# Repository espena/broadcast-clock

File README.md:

# Broadcast clock

**Digital precision studio/broadcast master clock with WiFi configuration, NTP client/server and GPS time sync.**

## Details

You'll find a complete project description on [my personal home page](https://espenandersen.no/esp32-broadcast-clock/ "Broadcast clock with ESP32 and NTP/GPS time receiver").

The enclosure is an 25x25 cm [IKEA "Sannahed"](https://www.ikea.com/us/en/p/sannahed-frame-black-60459118/) photo frame, which is deep enough to encapsulate the circuitry. I replaced the provided plexi glass with a dark acrylic glass plate.

There are no traditional buttons to control the clock. Instead, it has a browser based web configurator. When powered on, the clock will expose a dedicated wifi network for 30 seconds. Connect to the network in order to access the clock's control panel.

The clock supports time synchronization over the web (NTP) or via a range of GNSS satellite systems (GPS/QZSS, GLONASS, BeiDou, Galileo). It acts as a highly accurate NTP time server for other clocks on your LAN.

LED brightness is auto-adjusted to ambient light conditions. This feature can be overridden in the control panel.

It also has a stopwatch and a countdown timer that is operated from the browser interface.

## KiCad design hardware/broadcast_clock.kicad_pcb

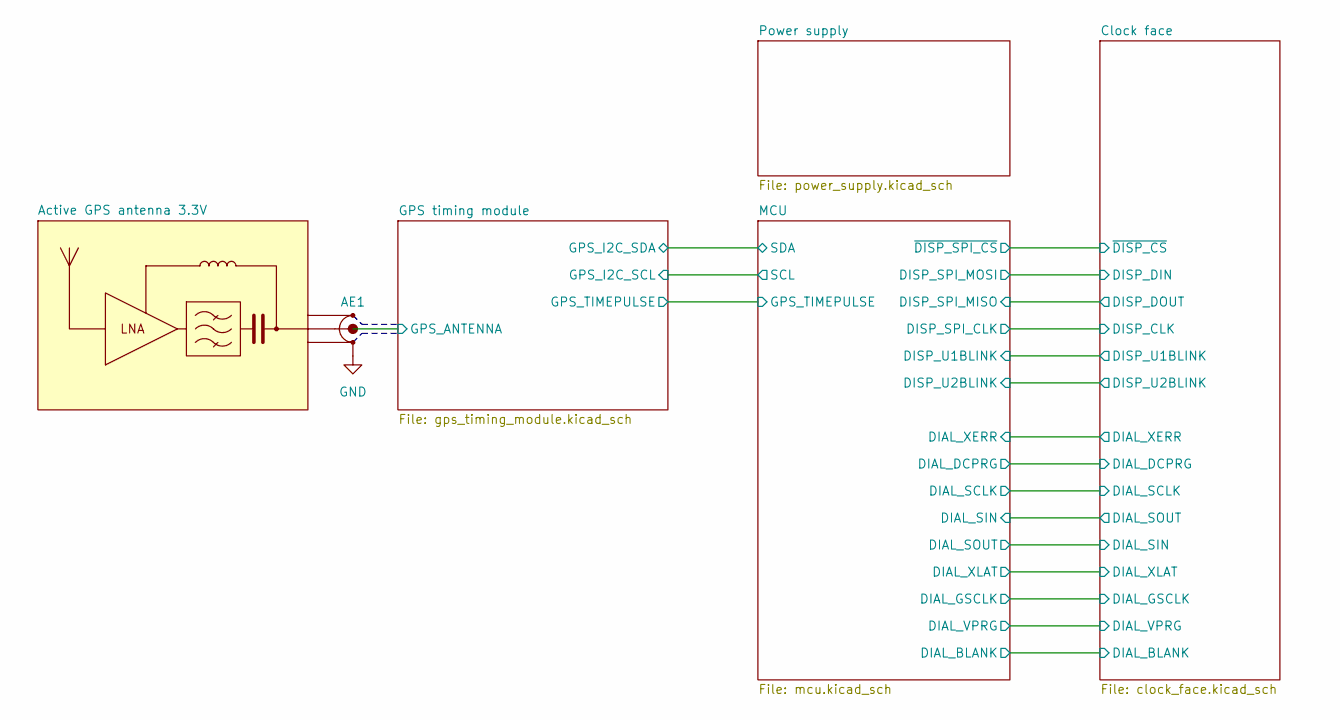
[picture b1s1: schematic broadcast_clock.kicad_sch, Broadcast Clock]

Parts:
AE1: Active GPS antenna 3.3V; SMA_Amphenol_132291-12_Vertical

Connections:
/GPS timing module/GPS_ANTENNA: AE1.1 (ANT); also elsewhere on the board

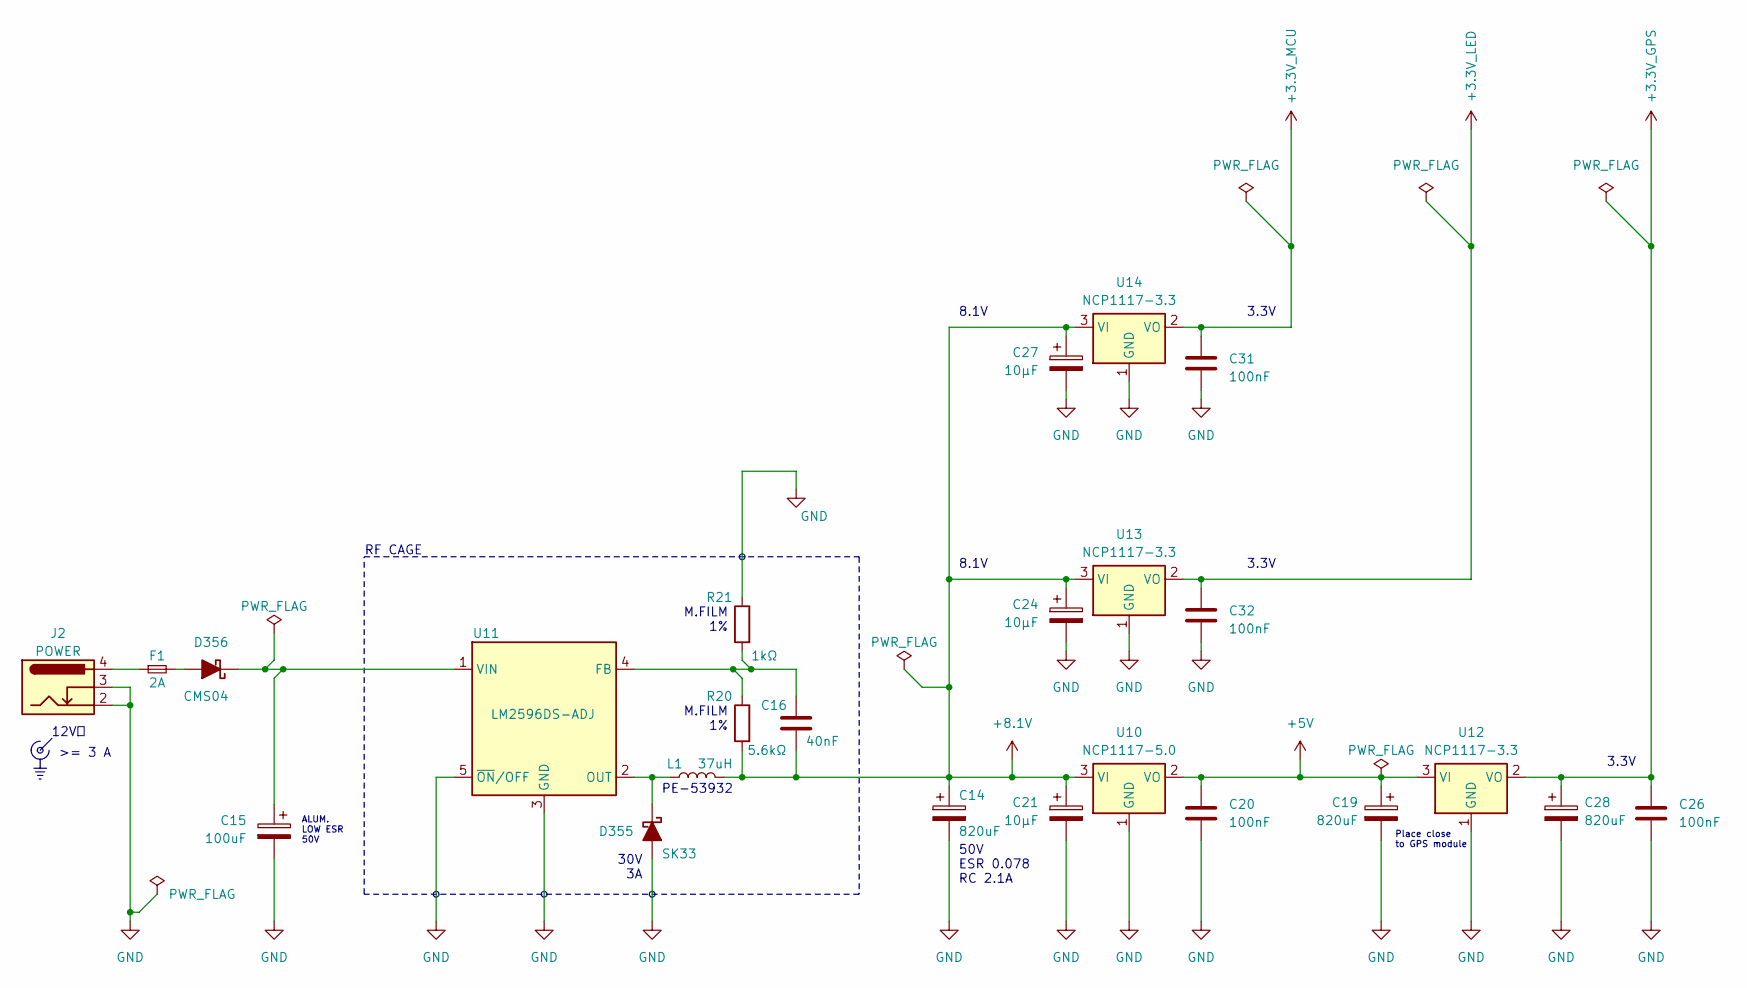
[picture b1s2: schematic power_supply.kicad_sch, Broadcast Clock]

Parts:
C14, C19, C28: 820uF; CP_Elec_18x16.5
C15: 100uF; CP_Elec_8x10
C16: 40nF; C_0805_2012Metric
C20, C26, C31, C32: 100nF; C_0805_2012Metric
C21, C24, C27: 10µF; C_0805_2012Metric
D355: SK33; D_SMA
D356: CMS04; SODFL4724X108N
F1: 2A; FuseHolder_Keystone_3554
J2: POWER; BarrelJack_DC044_Horizontal
L1: 37uH; L_Pulse_LCI-44
R20: 5.6kΩ; R_0805_2012Metric
R21: 1kΩ; R_0805_2012Metric
U10: NCP1117-5.0; SOT-223-3_TabPin2
U11: LM2596DS-ADJ; NCP5663DSADJR4G
U12, U13, U14: NCP1117-3.3; SOT-223-3_TabPin2

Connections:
+3.3V_GPS: C26.1, C28.1, U12.2 (VO); also elsewhere on the board
+5V: C19.1, C20.1, U10.2 (VO), U12.3 (VI)
+8.1V: C14.1, C16.2, C21.1, C24.1, C27.1, L1.2, R20.2, U10.3 (VI), U13.3 (VI), U14.3 (VI)
unnamed: D355.1 (K), L1.1, U11.2 (OUT)
unnamed: D356.2 (A), F1.2
unnamed: C15.1, D356.1 (K), U11.1 (VIN)
unnamed: F1.1, J2.4
unnamed: C16.1, R20.1, R21.2, U11.4 (FB)

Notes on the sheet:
M.FILM 1%
3.3V
ALUM. LOW ESR 50V
PE-53932
Place close to GPS module
RF CAGE
12V⎓
30V 3A
8.1V
>= 3 A
50V ESR 0.078 RC 2.1A

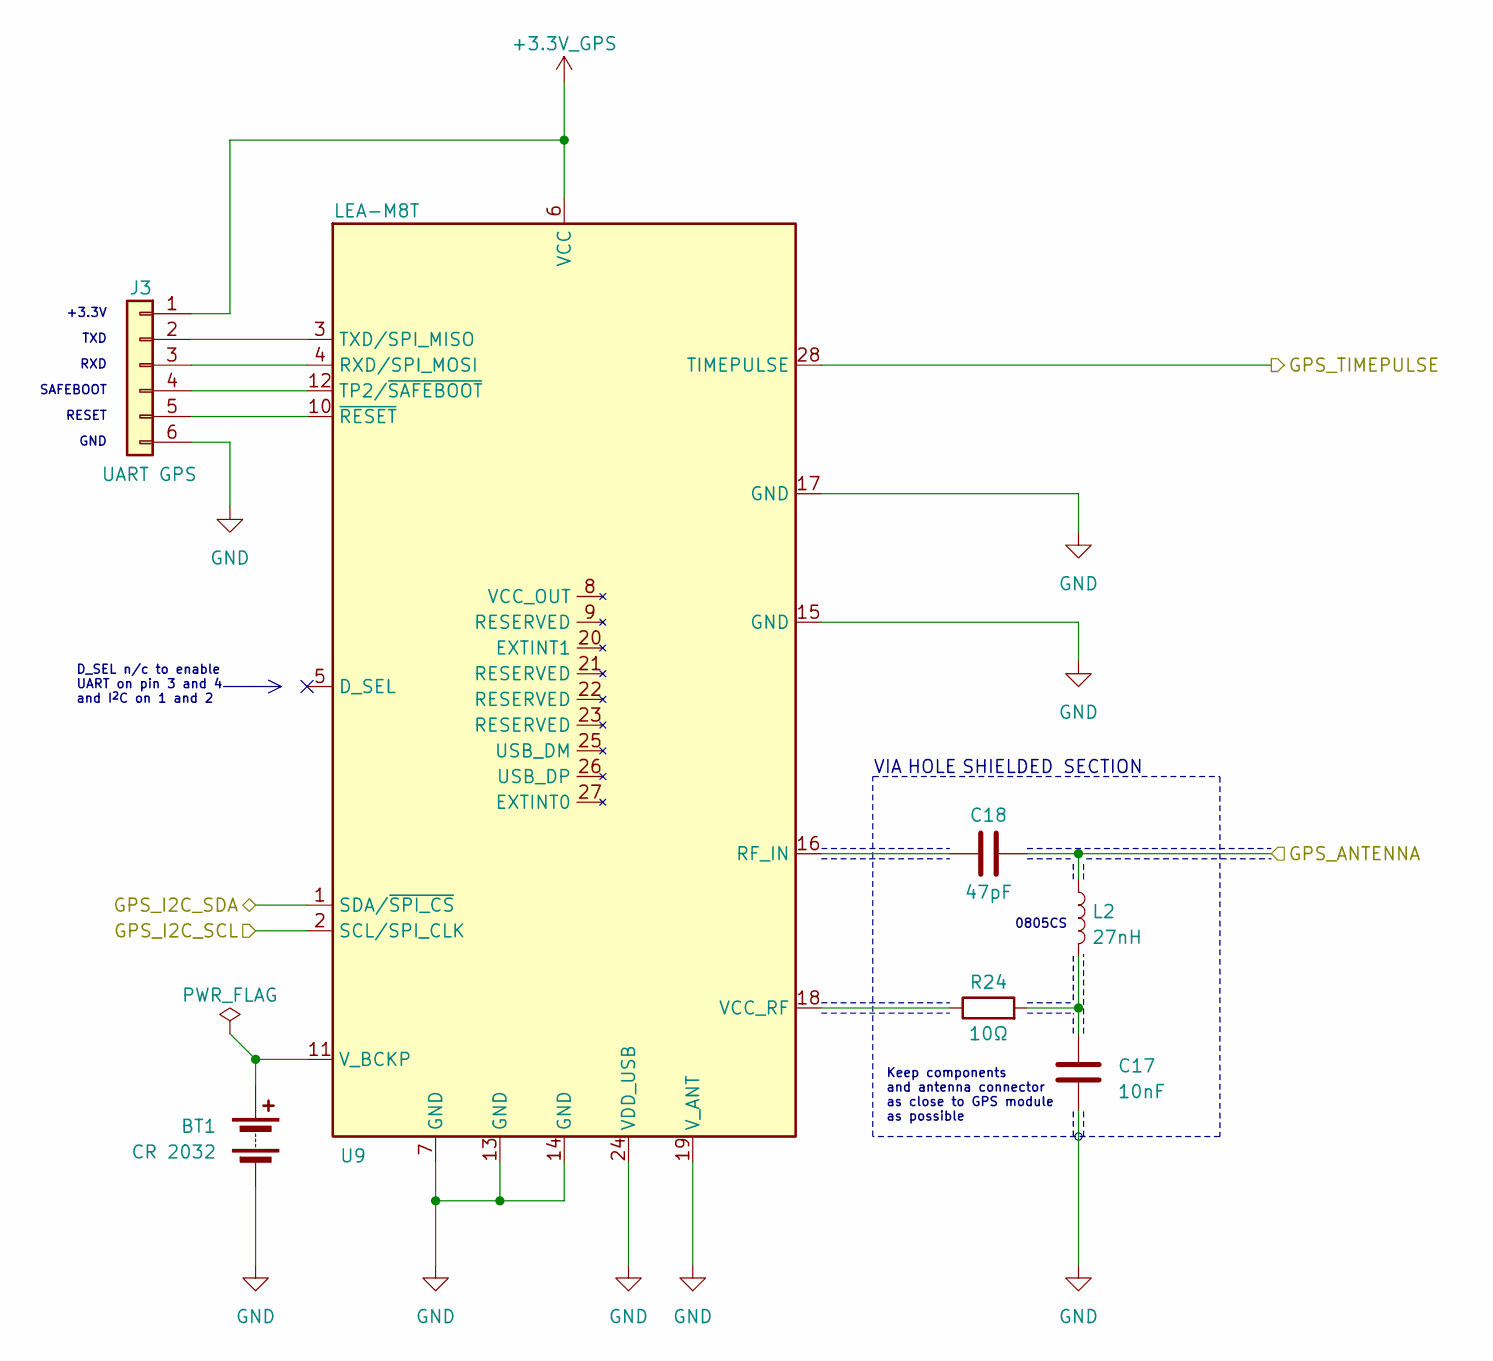
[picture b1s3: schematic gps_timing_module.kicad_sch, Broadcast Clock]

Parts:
BT1: CR 2032; BatteryHolder_Keystone_1058_1x2032
C17: 10nF; C_0805_2012Metric
C18: 47pF; C_0805_2012Metric
J3: UART GPS; PinHeader_1x06_P1.27mm_Vertical
L2: 27nH; L_Coilcraft_0805CS
R24: 10Ω; R_0805_2012Metric
U9: LEA-M8T; ublox_LEA

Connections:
+3.3V_GPS: J3.1, U9.6 (VCC); also elsewhere on the board
/GPS timing module/GPS_ANTENNA: C18.2, L2.1; also elsewhere on the board
/MCU/SCL: U9.2 (SCL/SPI_CLK); also elsewhere on the board
/MCU/SDA: U9.1 (SDA/~SPI_CS); also elsewhere on the board
unnamed: BT1.1 (+), U9.11 (V_BCKP)
unnamed: C17.1, L2.2, R24.2
unnamed: J3.2, U9.3 (TXD/SPI_MISO)
unnamed: J3.3, U9.4 (RXD/SPI_MOSI)
unnamed: J3.4, U9.12 (TP2/~SAFEBOOT)
unnamed: J3.5, U9.10 (~RESET)
unnamed: C18.1, U9.16 (RF_IN)
unnamed: R24.1, U9.18 (VCC_RF)

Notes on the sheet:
SAFEBOOT
0805CS
Keep components and antenna connector as close to GPS module as possible
D_SEL n/c to enable UART on pin 3 and 4 and I^{2}C on 1 and 2
RESET
VIA HOLE SHIELDED SECTION
RXD
GND
TXD
+3.3V

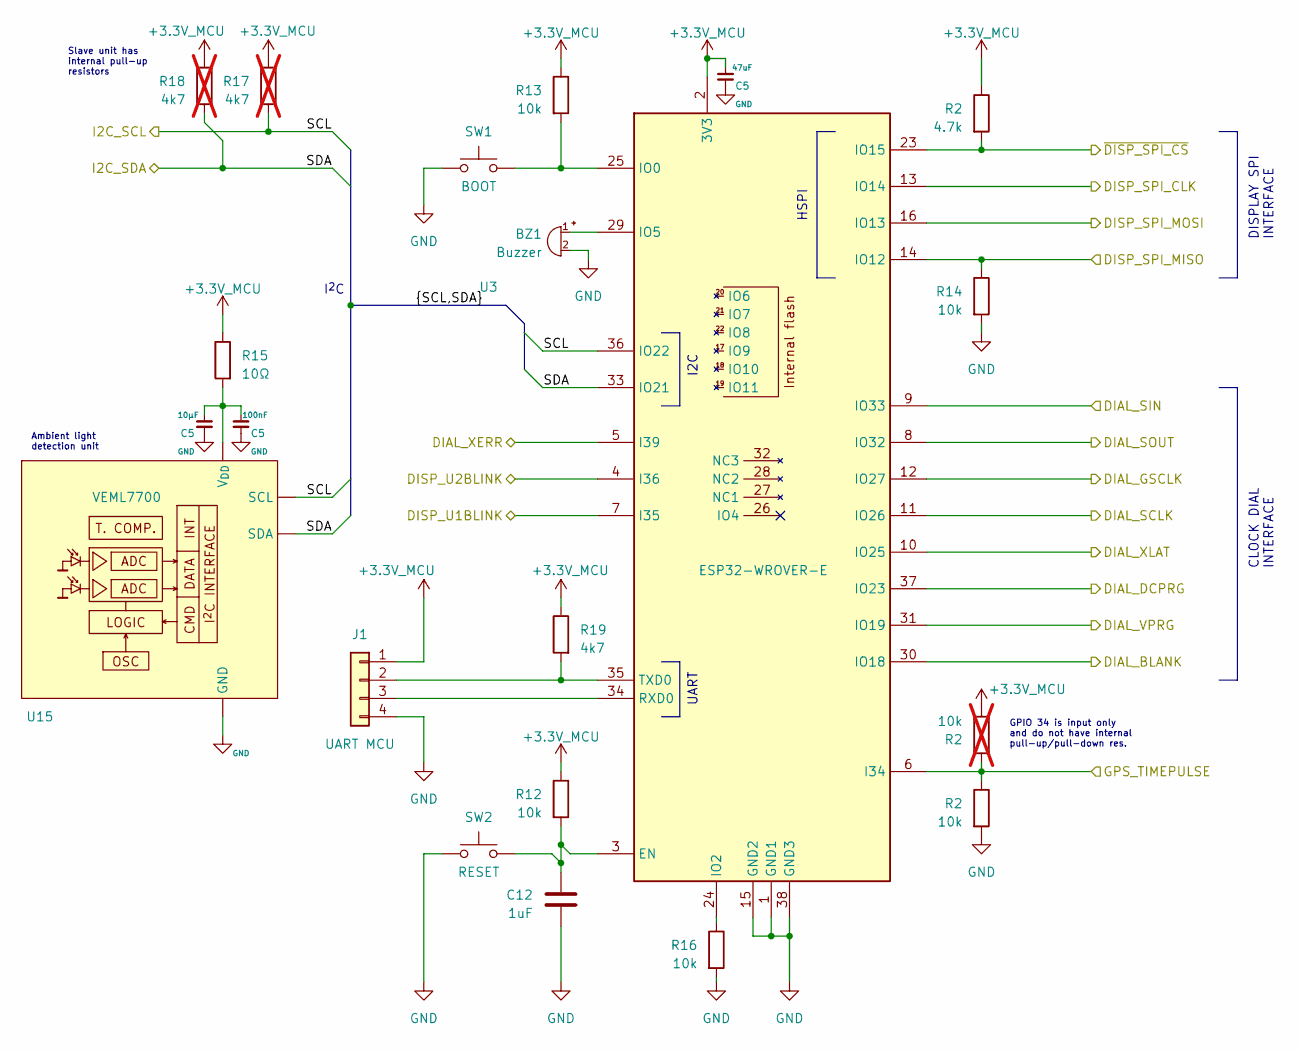
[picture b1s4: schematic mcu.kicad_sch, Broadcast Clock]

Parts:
BZ1: Buzzer; TP094003_Transducer_9x9mm
C5: 100nF; C_0805_2012Metric
C12: 1uF; C_0805_2012Metric
J1: UART MCU; Magnetic-Pogo-Female-MG0425FB_1x4_P2.54mm
R2: 4.7k; R_0805_2012Metric
R12, R13, R14, R16: 10k; R_0805_2012Metric
R15: 10Ω; R_0805_2012Metric
R17, R18: 4k7; R_0805_2012Metric; not fitted
R19: 4k7; R_0805_2012Metric
SW1: BOOT; SW_SPST_TL3301_6x6mm_H4.3mm
SW2: RESET; SW_SPST_TL3301_6x6mm_H4.3mm
U3: ESP32-WROVER-E; ESP32-WROVER-B_With_Cutout
U15: VEML7700

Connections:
/Clock face/DISP_U1BLINK: U3.7 (I35); also elsewhere on the board
/Clock face/DISP_U2BLINK: U3.4 (I36); also elsewhere on the board
/Clock face/LED dial/BLANK: U3.30 (IO18); also elsewhere on the board
/Clock face/LED dial/DCPRG: U3.37 (IO23); also elsewhere on the board
/Clock face/LED dial/GSCLK: U3.12 (IO27); also elsewhere on the board
/Clock face/LED dial/SCLK: U3.11 (IO26); also elsewhere on the board
/Clock face/LED dial/SIN: U3.8 (IO32); also elsewhere on the board
/Clock face/LED dial/SOUT: U3.9 (IO33); also elsewhere on the board
/Clock face/LED dial/VPRG: U3.31 (IO19); also elsewhere on the board
/Clock face/LED dial/XERR: U3.5 (I39); also elsewhere on the board
/Clock face/LED dial/XLAT: U3.10 (IO25); also elsewhere on the board
/Clock face/LED display/CLK: U3.13 (IO14); also elsewhere on the board
/Clock face/LED display/U1DIN: U3.16 (IO13); also elsewhere on the board
/Clock face/LED display/U2DOUT: R14.1, U3.14 (IO12); also elsewhere on the board
/MCU/SCL: R17.2, U3.36 (IO22), U15., U15.1 (SCL); also elsewhere on the board
/MCU/SDA: R18.2, U3.33 (IO21), U15., U15.4 (SDA); also elsewhere on the board
unnamed: BZ1.1 (-), U3.29 (IO5)
unnamed: J1.2, R19.2, U3.35 (TXD0)
unnamed: J1.3, U3.34 (RXD0)
unnamed: C12.1, R12.2, SW2.2, U3.3 (EN)
unnamed: R13.2, SW1.2, U3.25 (IO0)
unnamed: R16.1, U3.24 (IO2)

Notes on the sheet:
HSPI
I2C
CLOCK DIAL INTERFACE
Ambient light detection unit
DISPLAY SPI INTERFACE
GPIO 34 is input only and do not have internal pull-up/pull-down res.
Slave unit has internal pull-up resistors
UART
I^{2}C

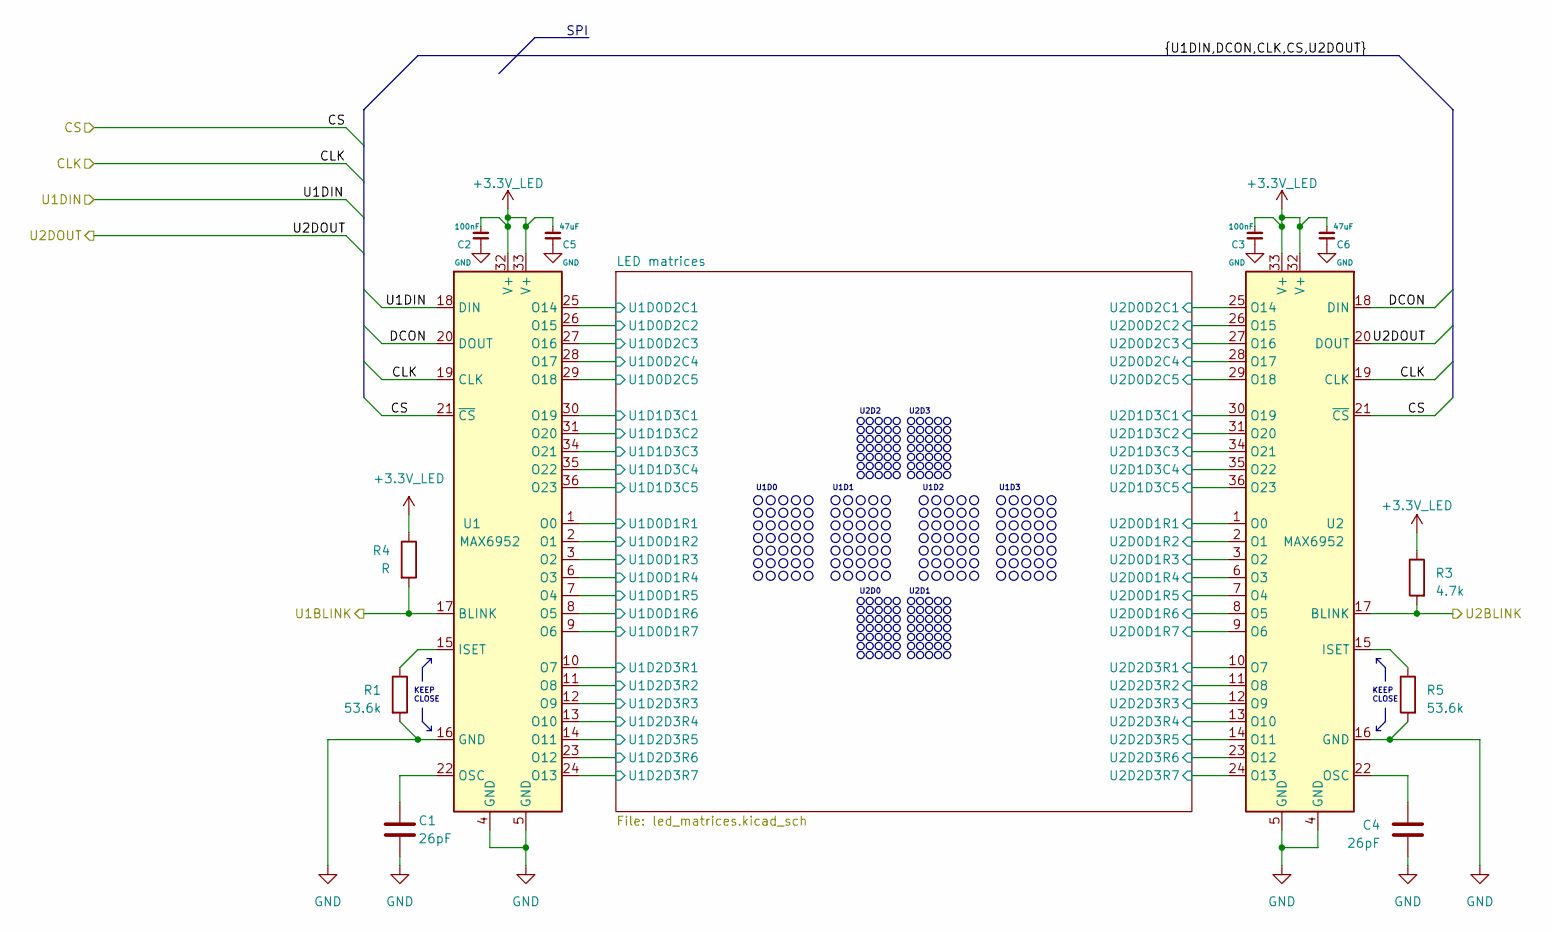
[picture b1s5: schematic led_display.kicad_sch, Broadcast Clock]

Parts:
C1, C4: 26pF; C_0805_2012Metric
C2, C3: 100nF; C_0805_2012Metric
C5, C6: 47uF; C_0805_2012Metric
R1, R5: 53.6k; R_0805_2012Metric
R3: 4.7k; R_0805_2012Metric
R4: R; R_0805_2012Metric
U1, U2: MAX6952; SSOP-36_7.5x12.5mm_P0.65mm

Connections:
/Clock face/DISP_U1BLINK: R4.2, U1.17 (BLINK); also elsewhere on the board
/Clock face/DISP_U2BLINK: R3.2, U2.17 (BLINK); also elsewhere on the board
/Clock face/LED display/CLK: U1.19 (CLK), U2.19 (CLK); also elsewhere on the board
/Clock face/LED display/DCON: U1.20 (DOUT), U2.18 (DIN)
/Clock face/LED display/LED matrices/U1D0D1R1: U1.1 (O0); also elsewhere on the board
/Clock face/LED display/LED matrices/U1D0D1R2: U1.2 (O1); also elsewhere on the board
/Clock face/LED display/LED matrices/U1D0D1R3: U1.3 (O2); also elsewhere on the board
/Clock face/LED display/LED matrices/U1D0D1R4: U1.6 (O3); also elsewhere on the board
/Clock face/LED display/LED matrices/U1D0D1R5: U1.7 (O4); also elsewhere on the board
/Clock face/LED display/LED matrices/U1D0D1R6: U1.8 (O5); also elsewhere on the board
/Clock face/LED display/LED matrices/U1D0D1R7: U1.9 (O6); also elsewhere on the board
/Clock face/LED display/LED matrices/U1D0D2C1: U1.25 (O14); also elsewhere on the board
/Clock face/LED display/LED matrices/U1D0D2C2: U1.26 (O15); also elsewhere on the board
/Clock face/LED display/LED matrices/U1D0D2C3: U1.27 (O16); also elsewhere on the board
/Clock face/LED display/LED matrices/U1D0D2C4: U1.28 (O17); also elsewhere on the board
/Clock face/LED display/LED matrices/U1D0D2C5: U1.29 (O18); also elsewhere on the board
/Clock face/LED display/LED matrices/U1D1D3C1: U1.30 (O19); also elsewhere on the board
/Clock face/LED display/LED matrices/U1D1D3C2: U1.31 (O20); also elsewhere on the board
/Clock face/LED display/LED matrices/U1D1D3C3: U1.34 (O21); also elsewhere on the board
/Clock face/LED display/LED matrices/U1D1D3C4: U1.35 (O22); also elsewhere on the board
/Clock face/LED display/LED matrices/U1D1D3C5: U1.36 (O23); also elsewhere on the board
/Clock face/LED display/LED matrices/U1D2D3R1: U1.10 (O7); also elsewhere on the board
/Clock face/LED display/LED matrices/U1D2D3R2: U1.11 (O8); also elsewhere on the board
/Clock face/LED display/LED matrices/U1D2D3R3: U1.12 (O9); also elsewhere on the board
/Clock face/LED display/LED matrices/U1D2D3R4: U1.13 (O10); also elsewhere on the board
/Clock face/LED display/LED matrices/U1D2D3R5: U1.14 (O11); also elsewhere on the board
/Clock face/LED display/LED matrices/U1D2D3R6: U1.23 (O12); also elsewhere on the board
/Clock face/LED display/LED matrices/U1D2D3R7: U1.24 (O13); also elsewhere on the board
/Clock face/LED display/LED matrices/U2D0D1R1: U2.1 (O0); also elsewhere on the board
/Clock face/LED display/LED matrices/U2D0D1R2: U2.2 (O1); also elsewhere on the board
/Clock face/LED display/LED matrices/U2D0D1R3: U2.3 (O2); also elsewhere on the board
/Clock face/LED display/LED matrices/U2D0D1R4: U2.6 (O3); also elsewhere on the board
/Clock face/LED display/LED matrices/U2D0D1R5: U2.7 (O4); also elsewhere on the board
/Clock face/LED display/LED matrices/U2D0D1R6: U2.8 (O5); also elsewhere on the board
/Clock face/LED display/LED matrices/U2D0D1R7: U2.9 (O6); also elsewhere on the board
/Clock face/LED display/LED matrices/U2D0D2C1: U2.25 (O14); also elsewhere on the board
/Clock face/LED display/LED matrices/U2D0D2C2: U2.26 (O15); also elsewhere on the board
/Clock face/LED display/LED matrices/U2D0D2C3: U2.27 (O16); also elsewhere on the board
/Clock face/LED display/LED matrices/U2D0D2C4: U2.28 (O17); also elsewhere on the board
/Clock face/LED display/LED matrices/U2D0D2C5: U2.29 (O18); also elsewhere on the board
/Clock face/LED display/LED matrices/U2D1D3C1: U2.30 (O19); also elsewhere on the board
/Clock face/LED display/LED matrices/U2D1D3C2: U2.31 (O20); also elsewhere on the board
/Clock face/LED display/LED matrices/U2D1D3C3: U2.34 (O21); also elsewhere on the board
/Clock face/LED display/LED matrices/U2D1D3C4: U2.35 (O22); also elsewhere on the board
/Clock face/LED display/LED matrices/U2D1D3C5: U2.36 (O23); also elsewhere on the board
/Clock face/LED display/LED matrices/U2D2D3R1: U2.10 (O7); also elsewhere on the board
/Clock face/LED display/LED matrices/U2D2D3R2: U2.11 (O8); also elsewhere on the board
/Clock face/LED display/LED matrices/U2D2D3R3: U2.12 (O9); also elsewhere on the board
/Clock face/LED display/LED matrices/U2D2D3R4: U2.13 (O10); also elsewhere on the board
/Clock face/LED display/LED matrices/U2D2D3R5: U2.14 (O11); also elsewhere on the board
/Clock face/LED display/LED matrices/U2D2D3R6: U2.23 (O12); also elsewhere on the board
/Clock face/LED display/LED matrices/U2D2D3R7: U2.24 (O13); also elsewhere on the board
/Clock face/LED display/U1DIN: U1.18 (DIN); also elsewhere on the board
/Clock face/LED display/U2DOUT: U2.20 (DOUT); also elsewhere on the board
unnamed: R1.1, U1.15 (ISET)
unnamed: C1.2, U1.22 (OSC)
unnamed: R5.1, U2.15 (ISET)
unnamed: C4.2, U2.22 (OSC)

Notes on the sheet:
U1D3
KEEP CLOSE
SPI
U1D2
U2D3
U1D0
U2D2
U1D1
U2D0
U2D1

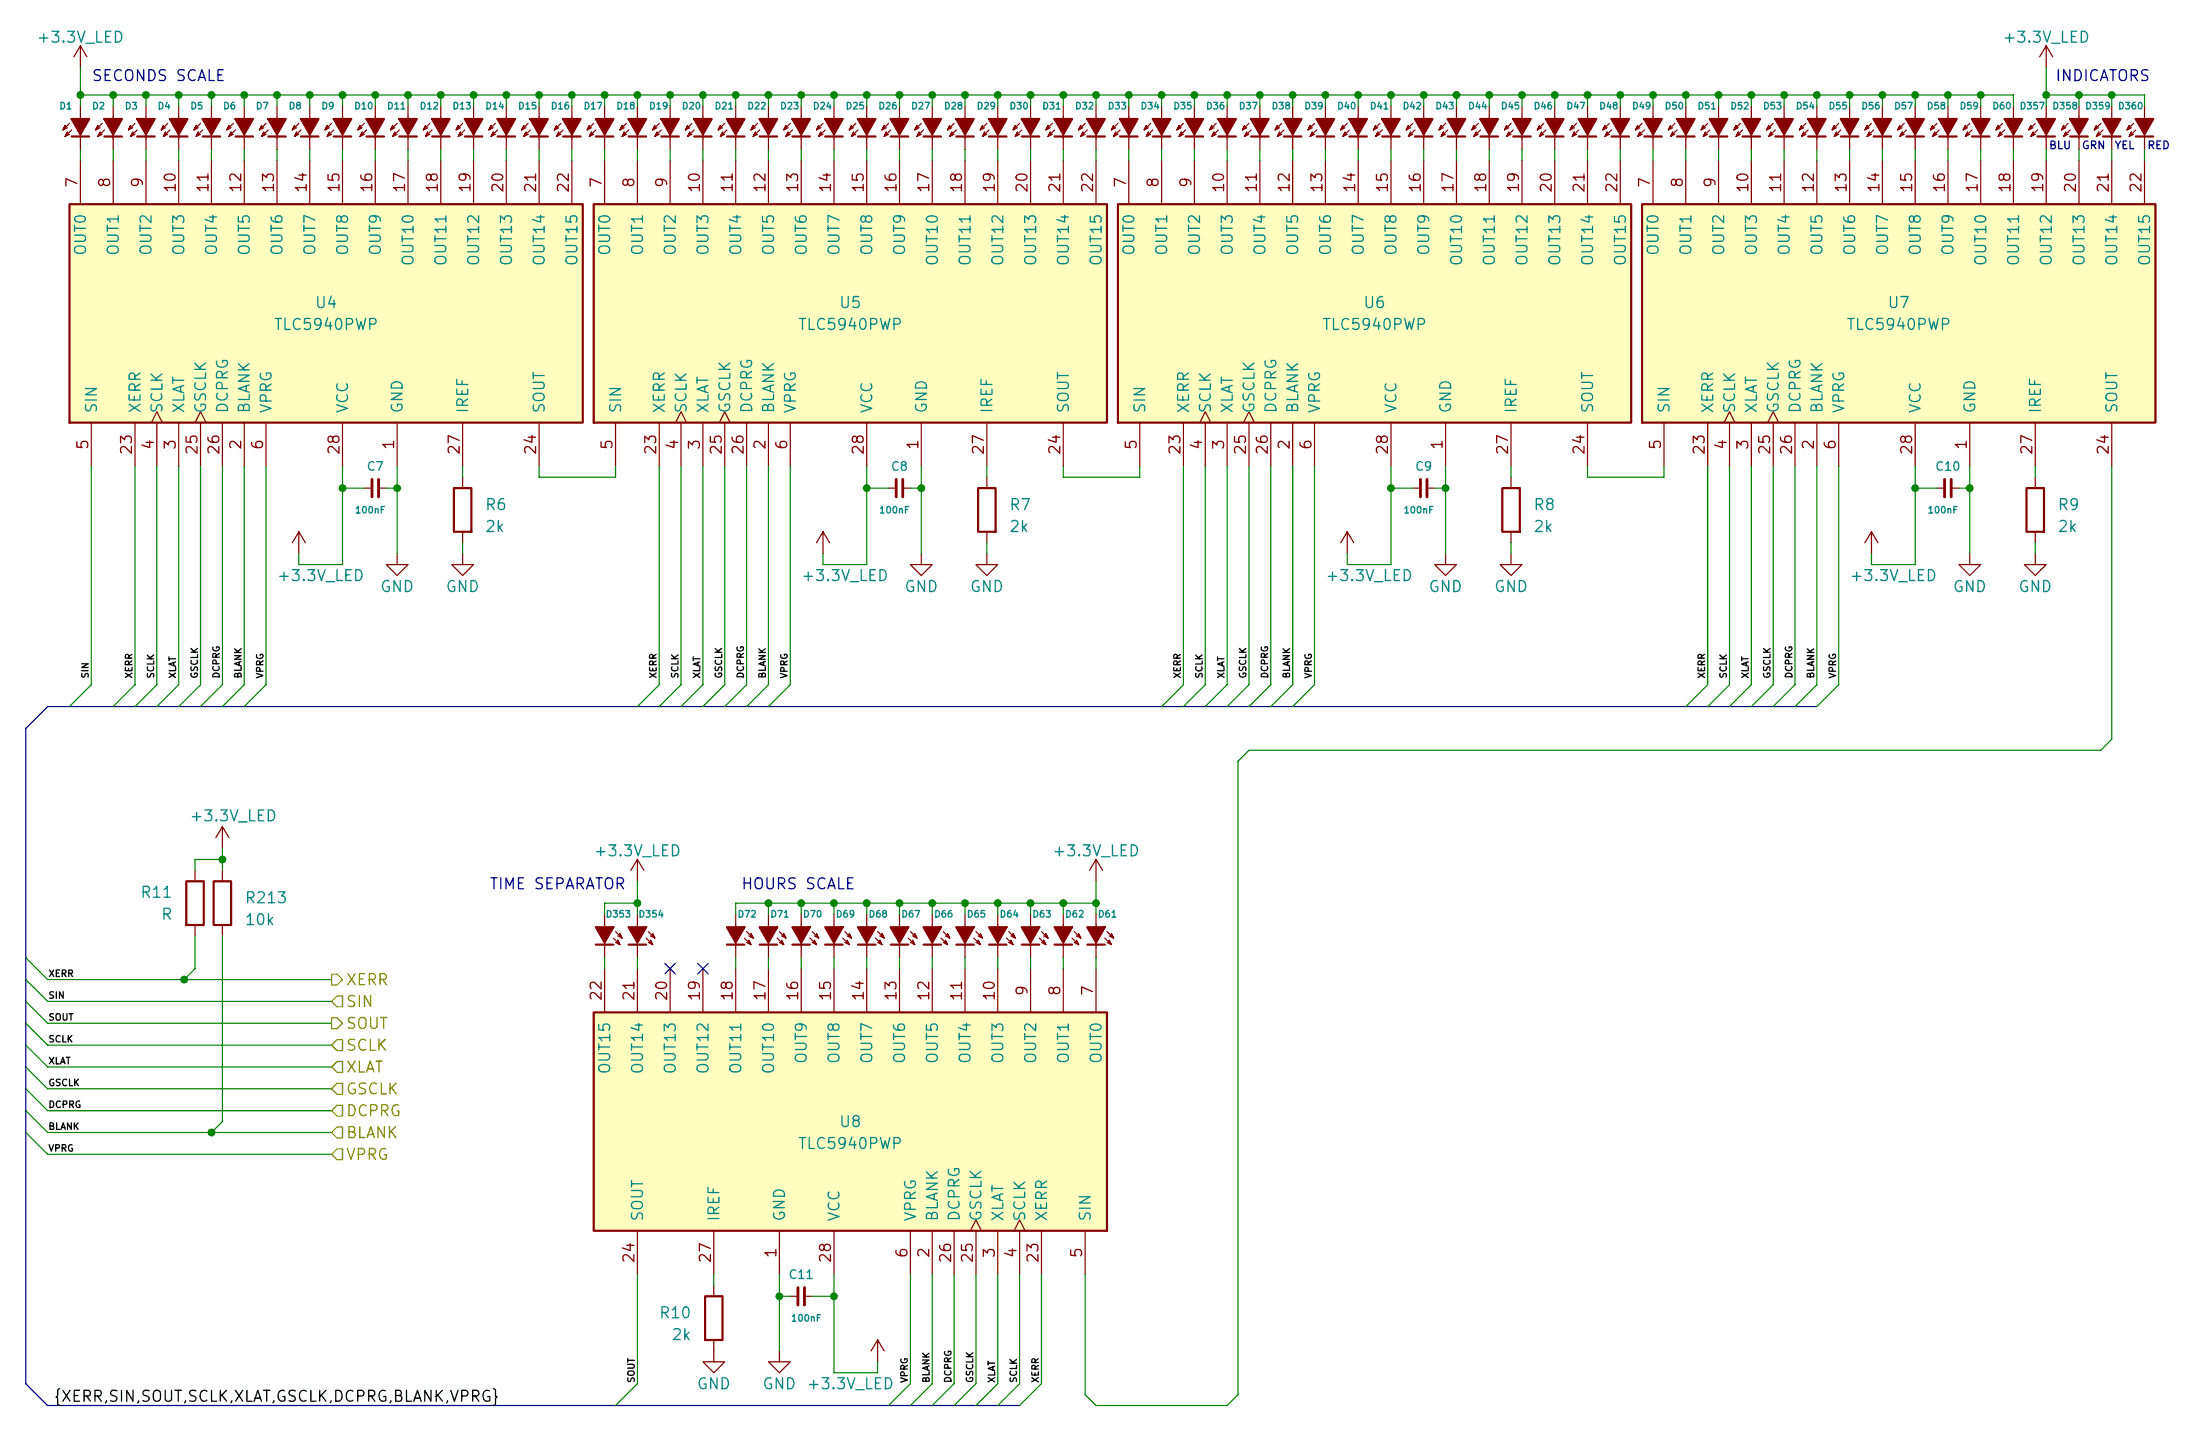
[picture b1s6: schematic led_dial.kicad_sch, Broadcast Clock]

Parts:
C7, C8, C9, C10, C11: 100nF; C_0805_2012Metric
D1, D2, D3, D4, D5, D6, D7, D8, D9, D10, D11, D12, D13, D14, D15, D16, D17, D18, D19, D20, D21, D22, D23, D24, D25, D26, D27, D28, D29, D30, D31, D32, D33, D34, D35, D36, D37, D38, D39, D40, D41, D42, D43, D44, D45, D46, D47, D48, D49, D50, D51, D52, D53, D54, D55, D56, D57, D58, D59, D60, D61, D62, D63, D64, D65, D66, D67, D68, D69, D70, D71, D72, D353, D354: 620nm; LED_D5.0mm_p2.54
D357: 470nm; LED_0805_2012Metric
D358: 570nm; LED_0805_2012Metric
D359: 590nm; LED_0805_2012Metric
D360: 620nm; LED_0805_2012Metric
R6, R7, R8, R9, R10: 2k; R_0805_2012Metric
R11: R; R_0805_2012Metric
R213: 10k; R_0805_2012Metric
U4, U5, U6, U7, U8: TLC5940PWP; HTSSOP-28-1EP_4.4x9.7mm_P0.65mm_EP3.4x9.5mm_Mask2.4x6.17mm_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

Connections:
/Clock face/LED dial/BLANK: R213.2, U4.2 (BLANK), U5.2 (BLANK), U6.2 (BLANK), U7.2 (BLANK), U8.2 (BLANK); also elsewhere on the board
/Clock face/LED dial/DCPRG: U4.26 (DCPRG), U5.26 (DCPRG), U6.26 (DCPRG), U7.26 (DCPRG), U8.26 (DCPRG); also elsewhere on the board
/Clock face/LED dial/GSCLK: U4.25 (GSCLK), U5.25 (GSCLK), U6.25 (GSCLK), U7.25 (GSCLK), U8.25 (GSCLK); also elsewhere on the board
/Clock face/LED dial/SCLK: U4.4 (SCLK), U5.4 (SCLK), U6.4 (SCLK), U7.4 (SCLK), U8.4 (SCLK); also elsewhere on the board
/Clock face/LED dial/SIN: U4.5 (SIN); also elsewhere on the board
/Clock face/LED dial/SOUT: U8.24 (SOUT); also elsewhere on the board
/Clock face/LED dial/VPRG: U4.6 (VPRG), U5.6 (VPRG), U6.6 (VPRG), U7.6 (VPRG), U8.6 (VPRG); also elsewhere on the board
/Clock face/LED dial/XERR: R11.2, U4.23 (XERR), U5.23 (XERR), U6.23 (XERR), U7.23 (XERR), U8.23 (XERR); also elsewhere on the board
/Clock face/LED dial/XLAT: U4.3 (XLAT), U5.3 (XLAT), U6.3 (XLAT), U7.3 (XLAT), U8.3 (XLAT); also elsewhere on the board
unnamed: D1.1 (K), U4.7 (OUT0)
unnamed: D2.1 (K), U4.8 (OUT1)
unnamed: D3.1 (K), U4.9 (OUT2)
unnamed: D4.1 (K), U4.10 (OUT3)
unnamed: D5.1 (K), U4.11 (OUT4)
unnamed: D6.1 (K), U4.12 (OUT5)
unnamed: D7.1 (K), U4.13 (OUT6)
unnamed: D8.1 (K), U4.14 (OUT7)
unnamed: D9.1 (K), U4.15 (OUT8)
unnamed: D10.1 (K), U4.16 (OUT9)
unnamed: D11.1 (K), U4.17 (OUT10)
unnamed: D12.1 (K), U4.18 (OUT11)
unnamed: D13.1 (K), U4.19 (OUT12)
unnamed: D14.1 (K), U4.20 (OUT13)
unnamed: D15.1 (K), U4.21 (OUT14)
unnamed: D16.1 (K), U4.22 (OUT15)
unnamed: D17.1 (K), U5.7 (OUT0)
unnamed: D18.1 (K), U5.8 (OUT1)
unnamed: D19.1 (K), U5.9 (OUT2)
unnamed: D20.1 (K), U5.10 (OUT3)
unnamed: D21.1 (K), U5.11 (OUT4)
unnamed: D22.1 (K), U5.12 (OUT5)
unnamed: D23.1 (K), U5.13 (OUT6)
unnamed: D24.1 (K), U5.14 (OUT7)
unnamed: D25.1 (K), U5.15 (OUT8)
unnamed: D26.1 (K), U5.16 (OUT9)
unnamed: D27.1 (K), U5.17 (OUT10)
unnamed: D28.1 (K), U5.18 (OUT11)
unnamed: D29.1 (K), U5.19 (OUT12)
unnamed: D30.1 (K), U5.20 (OUT13)
unnamed: D31.1 (K), U5.21 (OUT14)
unnamed: D32.1 (K), U5.22 (OUT15)
unnamed: D33.1 (K), U6.7 (OUT0)
unnamed: D34.1 (K), U6.8 (OUT1)
unnamed: D35.1 (K), U6.9 (OUT2)
unnamed: D36.1 (K), U6.10 (OUT3)
unnamed: D37.1 (K), U6.11 (OUT4)
unnamed: D38.1 (K), U6.12 (OUT5)
unnamed: D39.1 (K), U6.13 (OUT6)
unnamed: D40.1 (K), U6.14 (OUT7)
unnamed: D41.1 (K), U6.15 (OUT8)
unnamed: D42.1 (K), U6.16 (OUT9)
unnamed: D43.1 (K), U6.17 (OUT10)
unnamed: D44.1 (K), U6.18 (OUT11)
unnamed: D45.1 (K), U6.19 (OUT12)
unnamed: D46.1 (K), U6.20 (OUT13)
unnamed: D47.1 (K), U6.21 (OUT14)
unnamed: D48.1 (K), U6.22 (OUT15)
unnamed: D49.1 (K), U7.7 (OUT0)
unnamed: D50.1 (K), U7.8 (OUT1)
unnamed: D51.1 (K), U7.9 (OUT2)
unnamed: D52.1 (K), U7.10 (OUT3)
unnamed: D53.1 (K), U7.11 (OUT4)
unnamed: D54.1 (K), U7.12 (OUT5)
unnamed: D55.1 (K), U7.13 (OUT6)
unnamed: D56.1 (K), U7.14 (OUT7)
unnamed: D57.1 (K), U7.15 (OUT8)
unnamed: D58.1 (K), U7.16 (OUT9)
unnamed: D59.1 (K), U7.17 (OUT10)
unnamed: D60.1 (K), U7.18 (OUT11)
unnamed: D61.1 (K), U8.7 (OUT0)
unnamed: D62.1 (K), U8.8 (OUT1)
unnamed: D63.1 (K), U8.9 (OUT2)
unnamed: D64.1 (K), U8.10 (OUT3)
unnamed: D65.1 (K), U8.11 (OUT4)
unnamed: D66.1 (K), U8.12 (OUT5)
unnamed: D67.1 (K), U8.13 (OUT6)
unnamed: D68.1 (K), U8.14 (OUT7)
unnamed: D69.1 (K), U8.15 (OUT8)
unnamed: D70.1 (K), U8.16 (OUT9)
unnamed: D71.1 (K), U8.17 (OUT10)
unnamed: D72.1 (K), U8.18 (OUT11)
unnamed: D353.1 (K), U8.22 (OUT15)
unnamed: D354.1 (K), U8.21 (OUT14)
unnamed: D357.1 (K), U7.19 (OUT12)
unnamed: D358.1 (K), U7.20 (OUT13)
unnamed: D359.1 (K), U7.21 (OUT14)
unnamed: D360.1 (K), U7.22 (OUT15)
unnamed: R6.1, U4.27 (IREF)
unnamed: U4.24 (SOUT), U5.5 (SIN)
unnamed: R7.1, U5.27 (IREF)
unnamed: U5.24 (SOUT), U6.5 (SIN)
unnamed: R8.1, U6.27 (IREF)
unnamed: U6.24 (SOUT), U7.5 (SIN)
unnamed: R9.1, U7.27 (IREF)
unnamed: U7.24 (SOUT), U8.5 (SIN)
unnamed: R10.1, U8.27 (IREF)

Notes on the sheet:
BLU
YEL
HOURS SCALE
SECONDS SCALE
RED
INDICATORS
TIME SEPARATOR
GRN
